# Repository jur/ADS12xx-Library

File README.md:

# ADS12xx-Library
Library for connecting the Ti ADS1248 and ADS1256 24bit ADC to the Arduino Uno

##Example
The ADS12xx-Library.ino provides an example on how to implement and test the ads hardware.

## Schematic

The schematic shows an example how to connect ADS1248 and a 2 wire PT1000 to an
arduino uno. To test it, you can upload the ADS12xx-Library.ino after building
and connect via serial monitor. You enter the test mode with "t" and select
voltage measurement "4". It prints a value which represents the measured
voltage and is related to the temparatur.

## License 
The MIT License (MIT)
Copyright (c) 2016 Jonathan Graesser

Permission is hereby granted, free of charge, to any person obtaining a copy
of this software and associated documentation files (the "Software"), to deal
in the Software without restriction, including without limitation the rights
to use, copy, modify, merge, publish, distribute, sublicense, and/or sell
copies of the Software, and to permit persons to whom the Software is
furnished to do so, subject to the following conditions:

The above copyright notice and this permission notice shall be included in all
copies or substantial portions of the Software.

THE SOFTWARE IS PROVIDED "AS IS", WITHOUT WARRANTY OF ANY KIND, EXPRESS OR
IMPLIED, INCLUDING BUT NOT LIMITED TO THE WARRANTIES OF MERCHANTABILITY,
FITNESS FOR A PARTICULAR PURPOSE AND NONINFRINGEMENT. IN NO EVENT SHALL THE
AUTHORS OR COPYRIGHT HOLDERS BE LIABLE FOR ANY CLAIM, DAMAGES OR OTHER
LIABILITY, WHETHER IN AN ACTION OF CONTRACT, TORT OR OTHERWISE, ARISING FROM,
OUT OF OR IN CONNECTION WITH THE SOFTWARE OR THE USE OR OTHER DEALINGS IN THE
SOFTWARE.

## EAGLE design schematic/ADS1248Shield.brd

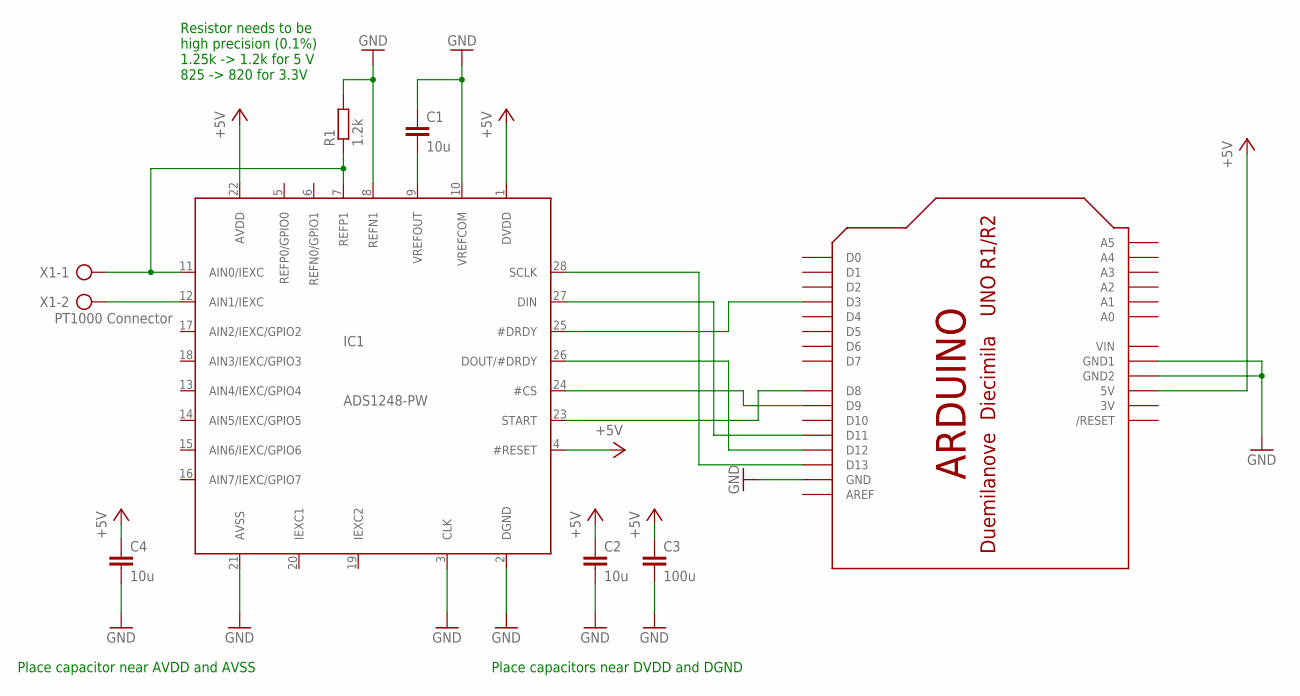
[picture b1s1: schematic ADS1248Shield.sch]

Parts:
C1, C2, C4: 10u; C2.5-4
C3: 100u; C2.5-4
IC1: ADS1248-PW; TSSOP28
R1: 1.2k; 0204V
U$1: ARDUINOUNO; ARDUINO
X1: PT1000 Connector; AK300/2

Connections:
3V: U$1.3V
+5V: C2.1, C3.1, C4.1, IC1.1 (DVDD), IC1.4 (#RESET), IC1.22 (AVDD), U$1.5V
GND: C1.1, C2.2, C3.2, C4.2, IC1.2 (DGND), IC1.3 (CLK), IC1.8 (REFN1), IC1.10 (VREFCOM), IC1.21 (AVSS), R1.2, U$1.GND, U$1.GND1, U$1.GND2
unnamed: IC1.7 (REFP1), IC1.11 (AIN0/IEXC), R1.1, X1.1
unnamed: IC1.28 (SCLK), U$1.D13
unnamed: IC1.12 (AIN1/IEXC), X1.2
unnamed: IC1.27 (DIN), U$1.D11
unnamed: IC1.25 (#DRDY), U$1.D3
unnamed: IC1.26 (DOUT/#DRDY), U$1.D12
unnamed: IC1.24 (#CS), U$1.D9
unnamed: IC1.23 (START), U$1.D8
unnamed: C1.2, IC1.9 (VREFOUT)
VIN: U$1.VIN

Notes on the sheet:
Place capacitor near AVDD and AVSS
Place capacitors near DVDD and DGND
Resistor needs to be high precision (0.1%) 1.25k -> 1.2k for 5 V 825 -> 820 for 3.3V

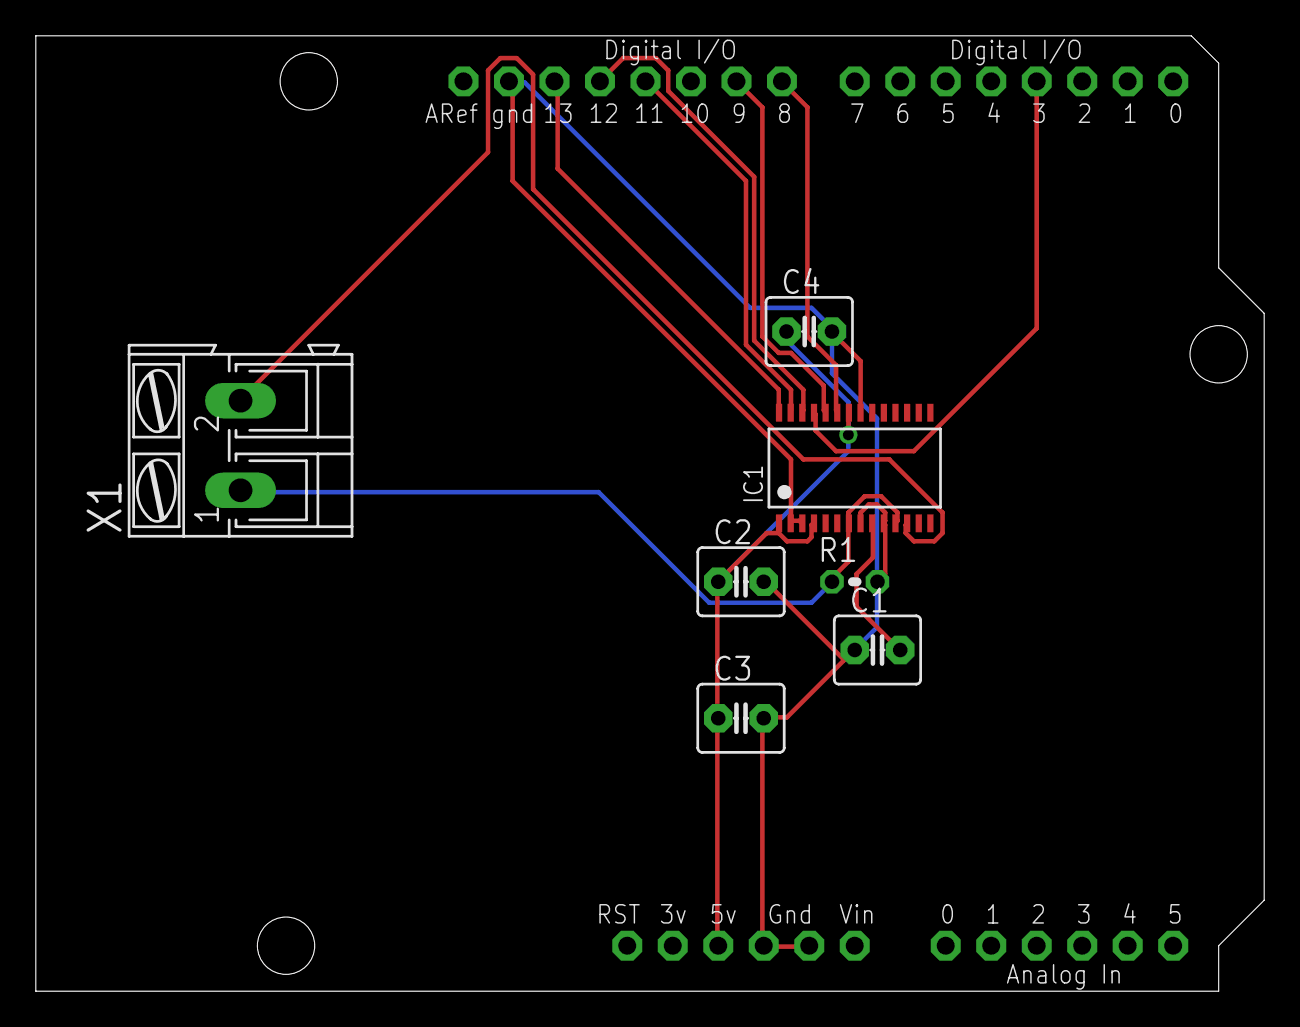
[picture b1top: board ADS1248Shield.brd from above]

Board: 2 copper layers, 68.6 x 53.3 mm, 8 parts (0 on the bottom side), 11 nets.

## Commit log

2016-06-26 Support Arduino UNO and PT1000.
    Add schematic for PT1000 with Arduino Uno.
    Added ADS1248 Shield for one PT1000 temparatur sensor.
    Use AIN0 and AIN1 for PT1000.
2016-06-26 Add description for PT1000 test
    Add link to schematic and describe test.
2016-07-03 Calculate temperature.
